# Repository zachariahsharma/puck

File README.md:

# Vynte Puck

KiCad hardware design for the Vynte room-temperature puck, part of a room-by-room HVAC comfort system.

## Open the project

Open `Puck.kicad_pro` in KiCad. The main schematic and PCB are `Puck.kicad_sch` and `Puck.kicad_pcb`. Supporting sheets cover the temperature sensor, seven-segment display, voltage regulator, USB Type-C receptacle, and external programming interface. Custom symbols, footprints, models, and a sensor datasheet are included in `Comps/`. Library tables are included at the project root.

## Saved fabrication files

`production/` contains the existing `Puck_0.5.0.zip` fabrication archive, BOM/designator/placement CSV exports, IPC netlist, and stencil layers. `fabrication-toolkit-options.json` preserves the export settings. These files are archived exports, not a verified manufacturing release. Regenerate fabrication files from the intended design and review DRC/ERC before ordering boards.

## Synchronization status

This snapshot preserves the saved local design as of October 26, 2026. Its source branch started at `d32a3a6`, while Gitea main had advanced by 14 commits to `c4a697f`. Combining the branches produces conflicts in `Puck.kicad_pcb`, `Puck.kicad_sch`, and `Puck.kicad_pro`. The saved design is submitted as a pull request for review; it has not been reconciled with or merged into main.

The public GitHub copy includes the development history and branch tips. Credential files have been removed throughout that history. Imported commits use Zachariah K. Sharma’s GitHub identity; original authors are credited in commit-message trailers. Rewriting this metadata changes commit IDs while preserving dates, changes, and merge structure. `main` retains the saved local design; `gitea-main` retains the upstream main branch, and the other development branches are also available. Gitea remains the development repository. Local backups, analysis caches, and per-user KiCad settings are excluded.

No open-source license has been selected.

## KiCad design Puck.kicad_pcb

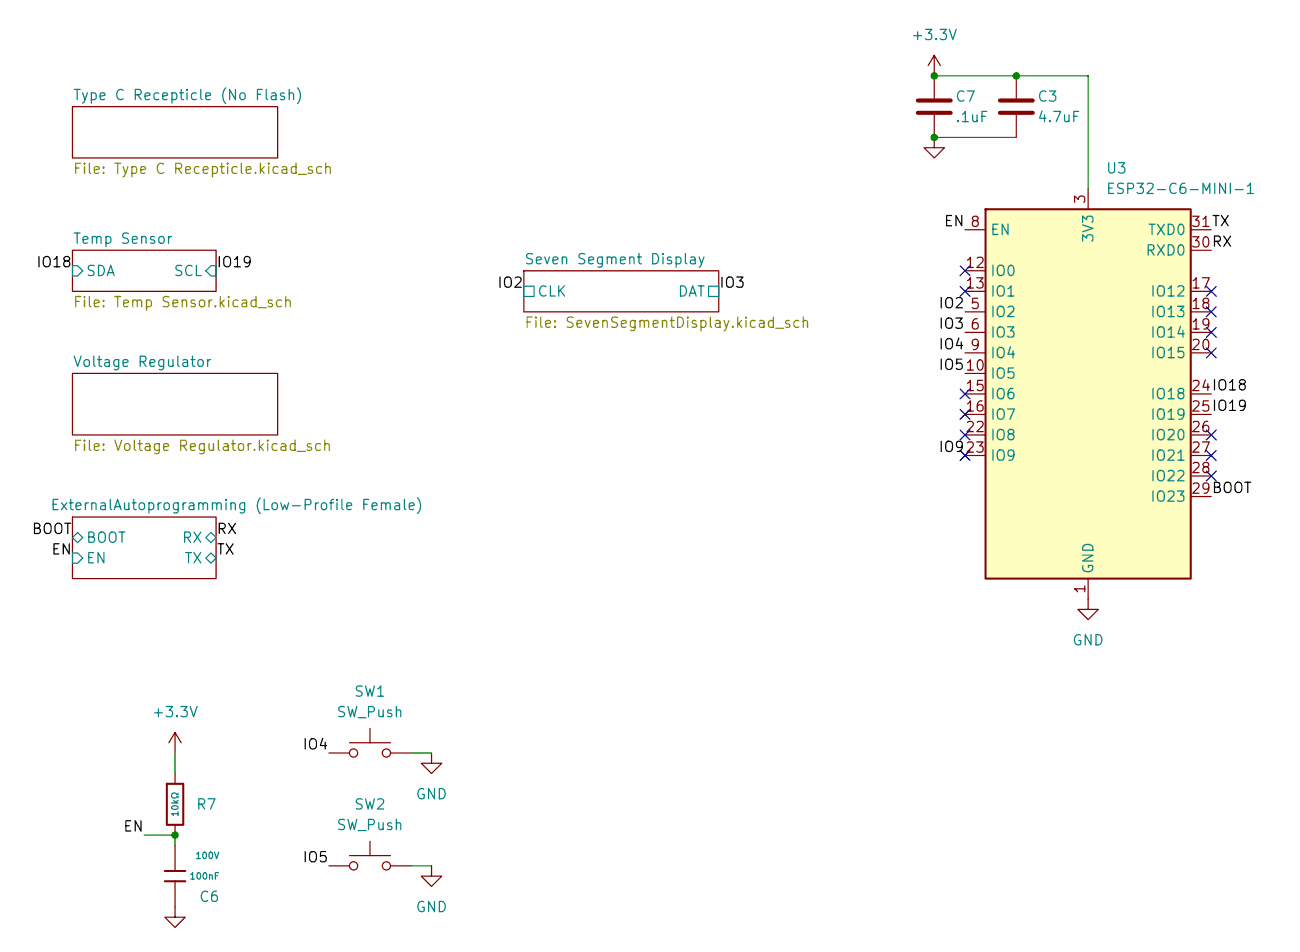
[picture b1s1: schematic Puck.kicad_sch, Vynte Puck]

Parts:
C3: 4.7uF; C_0603; MPN CL10A475KO8NNNC; DigiKey 1276-1784-2-ND
C6: 100nF; C_0805; Voltage Rated 100V; Tolerance ±10%; MPN CL21B104KCFNNNE; LCSC C28233
C7: .1uF; C_0603; MPN CL10B104KB8NNNC; DigiKey 1276-1000-2-ND
R7: 10kΩ; R_0603; Overload Voltage (Max) 75V; Tolerance ±1%; MPN 0603WAF1002T5E; LCSC C25804
SW1, SW2: SW_Push; SW_PUSH_6mm_H7.3mm; MPN B3F-4055; DigiKey SW414-ND
U3: ESP32-C6-MINI-1; MPN ESP32-C6-MINI-1-N4; LCSC C5736265

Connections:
+3.3V: C3.1, C7.1, R7.1, U3.3 (3V3); also elsewhere on the board
/BOOT: U3.29 (IO23); also elsewhere on the board
/EN: C6.1, R7.2, U3.8 (EN); also elsewhere on the board
/IO2: U3.5 (IO2); also elsewhere on the board
/IO3: U3.6 (IO3); also elsewhere on the board
/IO4: SW1.1, U3.9 (IO4)
/IO5: SW2.1, U3.10 (IO5)
/IO9: U3.23 (IO9)
/IO18: U3.24 (IO18); also elsewhere on the board
/IO19: U3.25 (IO19); also elsewhere on the board
/RX: U3.30 (RXD0); also elsewhere on the board
/TX: U3.31 (TXD0); also elsewhere on the board
GND: C3.2, C6.2, C7.2, SW1.2, SW2.2, U3.1 (GND), U3.2 (GND), U3.11 (GND), U3.14 (GND), U3.36 (GND), U3.37 (GND), U3.38 (GND), U3.39 (GND), U3.40 (GND), U3.41 (GND), U3.42 (GND), U3.43 (GND), U3.44 (GND), U3.45 (GND), U3.46 (GND), U3.47 (GND), U3.48 (GND), U3.49 (GND), U3.50 (GND), U3.51 (GND), U3.52 (GND), U3.53 (GND); also elsewhere on the board

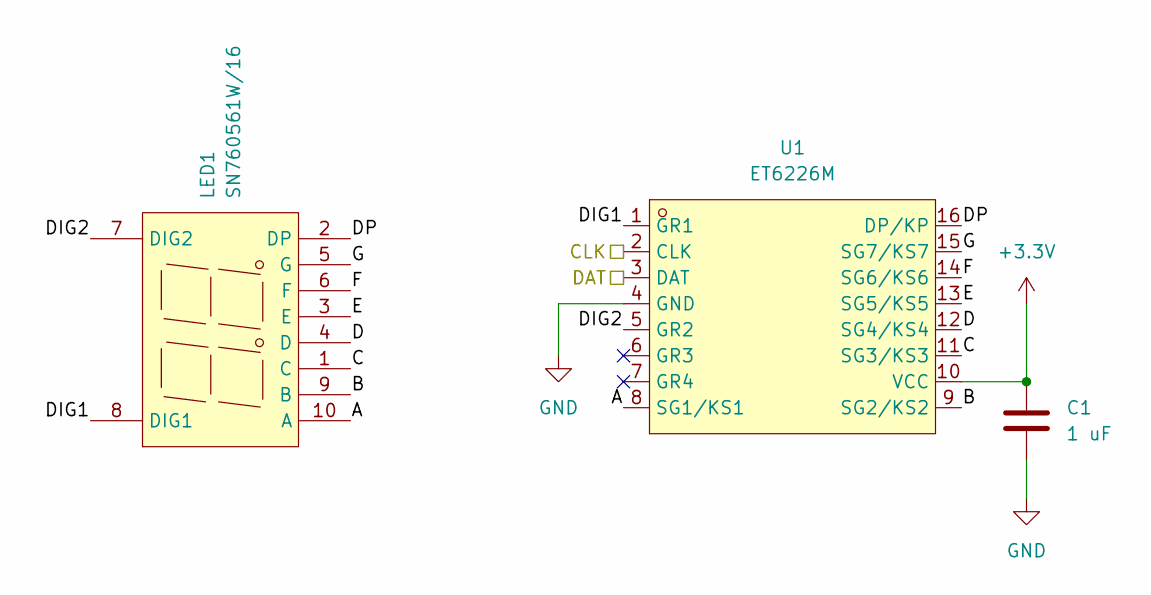
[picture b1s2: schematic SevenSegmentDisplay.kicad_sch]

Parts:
C1: 1 uF; C_0603; MPN CL10A105KB8NNNC; LCSC C15849
LED1: SN760561W/16; LED-SEG-TH_10P-L25.0-W19.0-P2.54-S15.2-BL; MPN SN760561W/16; LCSC C2980912
U1: ET6226M; SOP-16_L10.0-W3.9-P1.27-LS6.0-BL; MPN ET6226M; LCSC C347308

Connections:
+3.3V: C1.1, U1.10 (VCC); also elsewhere on the board
/IO2: U1.2 (CLK); also elsewhere on the board
/IO3: U1.3 (DAT); also elsewhere on the board
/Seven Segment Display/A: LED1.10 (A), U1.8 (SG1/KS1)
/Seven Segment Display/B: LED1.9 (B), U1.9 (SG2/KS2)
/Seven Segment Display/C: LED1.1 (C), U1.11 (SG3/KS3)
/Seven Segment Display/D: LED1.4 (D), U1.12 (SG4/KS4)
/Seven Segment Display/DIG1: LED1.8 (DIG1), U1.1 (GR1)
/Seven Segment Display/DIG2: LED1.7 (DIG2), U1.5 (GR2)
/Seven Segment Display/DP: LED1.2 (DP), U1.16 (DP/KP)
/Seven Segment Display/E: LED1.3 (E), U1.13 (SG5/KS5)
/Seven Segment Display/F: LED1.6 (F), U1.14 (SG6/KS6)
/Seven Segment Display/G: LED1.5 (G), U1.15 (SG7/KS7)
GND: C1.2, U1.4 (GND); also elsewhere on the board

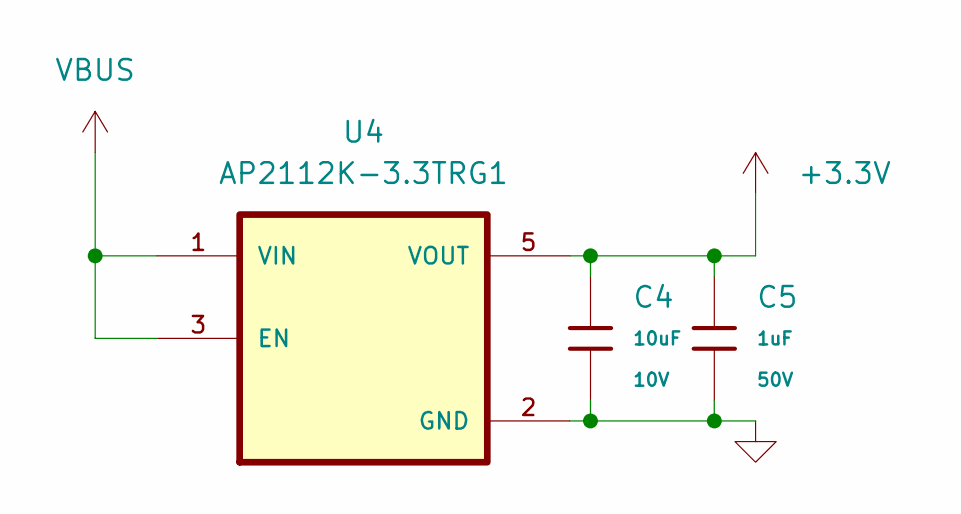
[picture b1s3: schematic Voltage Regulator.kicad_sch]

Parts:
C4: 10uF; C_0603; Voltage Rated 10V; Tolerance ±10%; MPN CL10A106KP8NNNC; LCSC C19702
C5: 1uF; C_0603; Voltage Rated 50V; Tolerance ±10%; MPN CL10A105KB8NNNC; LCSC C15849
U4: AP2112K-3.3TRG1; SOT95P285X140-5N; MPN AP2112K-3.3TRG1; LCSC C51118

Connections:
+3.3V: C4.1, C5.1, U4.5 (VOUT); also elsewhere on the board
GND: C4.2, C5.2, U4.2 (GND); also elsewhere on the board
VBUS: U4.1 (VIN), U4.3 (EN); also elsewhere on the board

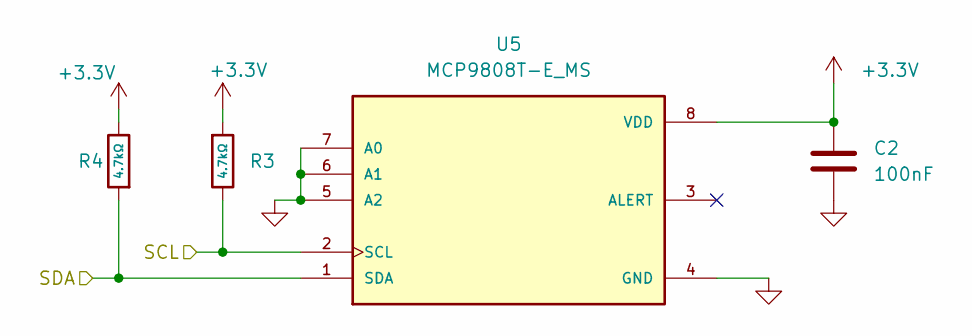
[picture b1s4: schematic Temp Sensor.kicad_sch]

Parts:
C2: 100nF; C_0603; MPN CL10B104KB8NNNC; DigiKey 1276-1000-2-ND
R3, R4: 4.7kΩ; R_0402; Overload Voltage (Max) 50V; Tolerance ±1%; MPN 0402WGF4701TCE; LCSC C25900
U5: MCP9808T-E_MS; SOP65P490X110-8N; MPN MCP9808T-E/MS; LCSC C129490

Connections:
+3.3V: C2.1, R3.1, R4.2, U5.8 (VDD); also elsewhere on the board
/IO18: R4.1, U5.1 (SDA); also elsewhere on the board
/IO19: R3.2, U5.2 (SCL); also elsewhere on the board
GND: C2.2, U5.4 (GND), U5.5 (A2), U5.6 (A1), U5.7 (A0); also elsewhere on the board

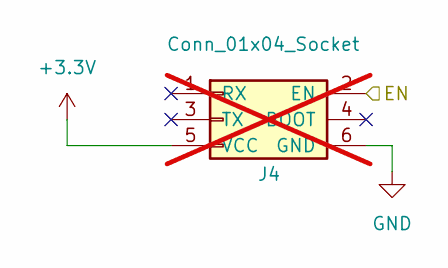
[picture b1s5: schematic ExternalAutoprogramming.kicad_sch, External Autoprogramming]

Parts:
J4: Conn_01x04_Socket; Tag-Connect_TC2030-IDC-NL_2x03_P1.27mm_Vertical; not fitted

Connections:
+3.3V: J4.5 (VCC); also elsewhere on the board
/BOOT: J4.4 (BOOT); also elsewhere on the board
/EN: J4.2 (EN); also elsewhere on the board
/RX: J4.1 (RX); also elsewhere on the board
/TX: J4.3 (TX); also elsewhere on the board
GND: J4.6 (GND); also elsewhere on the board

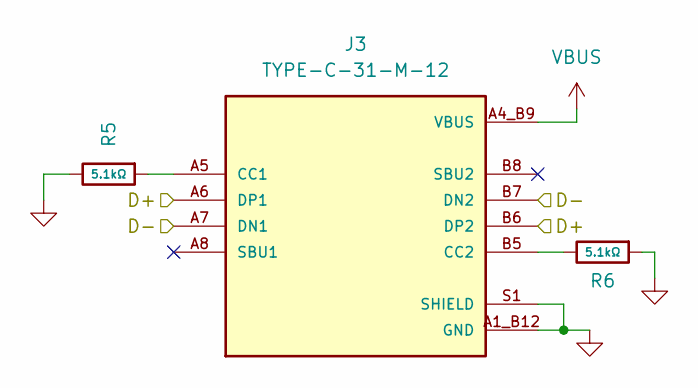
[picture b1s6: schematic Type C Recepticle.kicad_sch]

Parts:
J3: TYPE-C-31-M-12; HRO_TYPE-C-31-M-12; MPN TYPE-C-31-M-12; LCSC C165948
R5, R6: 5.1kΩ; R_0603; Overload Voltage (Max) 75V; Tolerance ±1%; MPN 0603WAF5101T5E; LCSC C23186

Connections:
GND: J3.A1_B12 (GND), J3.B1_A12 (GND), J3.S1 (SHIELD), J3.S2 (SHIELD), J3.S3 (SHIELD), J3.S4 (SHIELD), R5.2, R6.1; also elsewhere on the board
unnamed: J3.A5 (CC1), R5.1
unnamed: J3.B5 (CC2), R6.2
VBUS: J3.A4_B9 (VBUS), J3.B4_A9 (VBUS); also elsewhere on the board

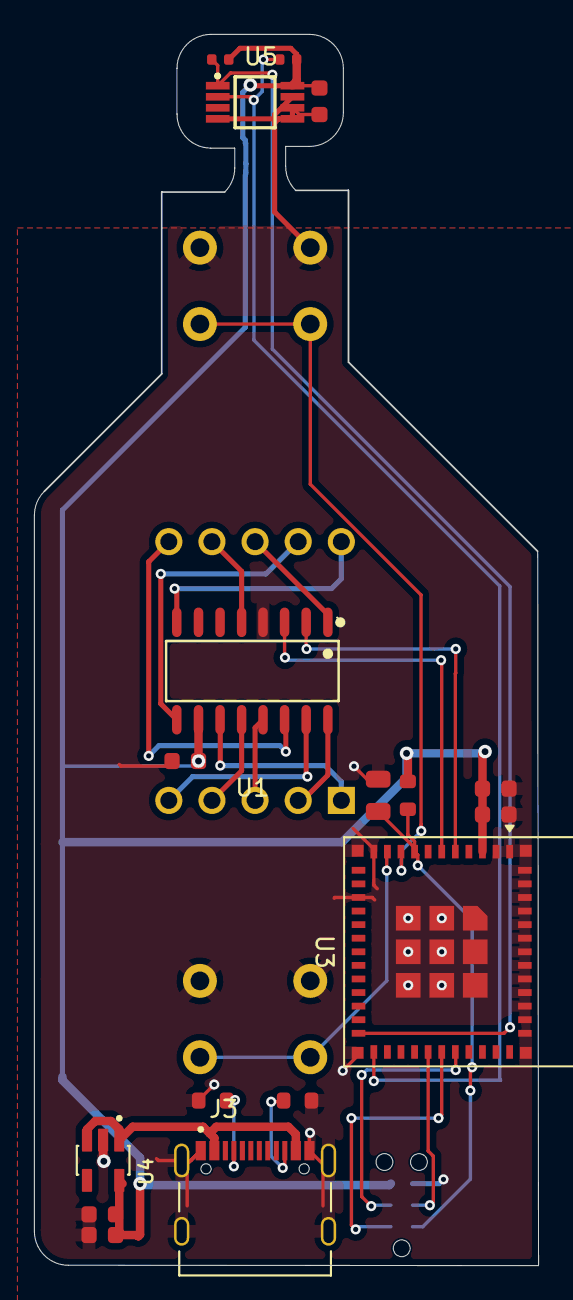
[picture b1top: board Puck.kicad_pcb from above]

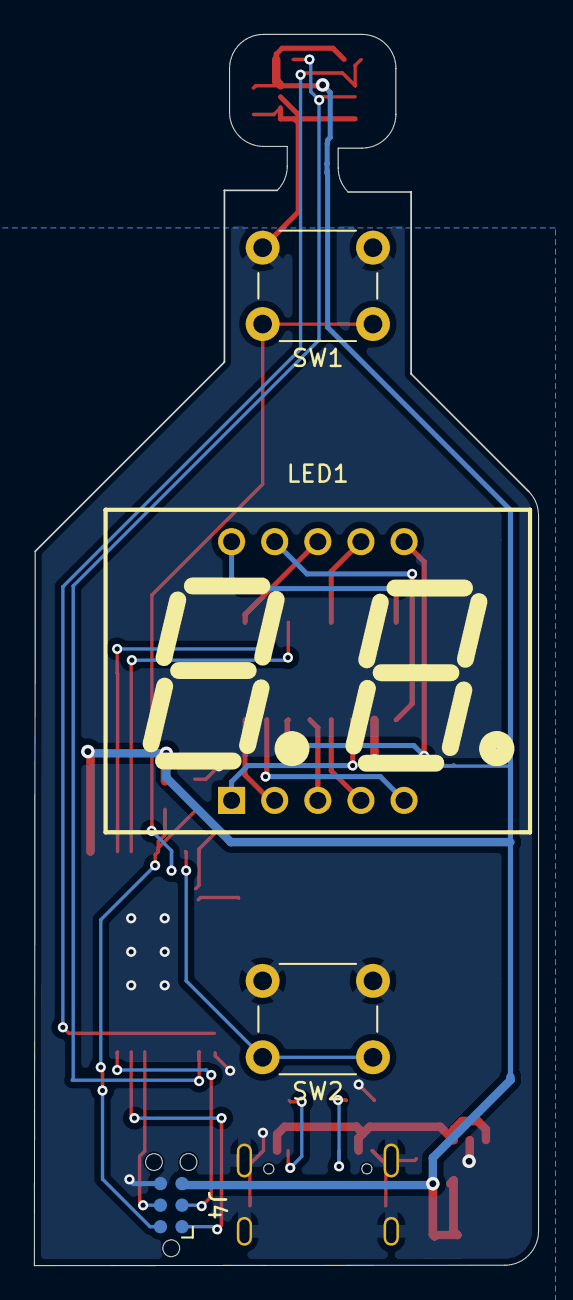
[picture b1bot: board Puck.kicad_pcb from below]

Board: 4 copper layers, 29.7 x 72.5 mm, 21 parts (4 on the bottom side), 25 nets.

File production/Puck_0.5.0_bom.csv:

Designator,Footprint,Quantity,Value,LCSC Part #
C1,C_0603,1,1 uF,C15849
C2,C_0603,1,100nF,C19702
C3,C_0603,1,4.7uF,C19702
C4,C_0603,1,10uF,C19702
C5,C_0603,1,1uF,C15849
C6,C_0805,1,100nF,C28233
C7,C_0603,1,.1uF,C19702
J3,HRO_TYPE-C-31-M-12,1,TYPE-C-31-M-12,C165948
LED1,LED-SEG-TH_10P-L25.0-W19.0-P2.54-S15.2-BL,1,SN760561W/16,C2980912
"R3, R4",R_0402,2,4.7kΩ,C25900
"R5, R6",R_0603,2,5.1kΩ,C23186
R7,R_0603,1,10kΩ,C25804
"SW1, SW2",SW_PUSH_6mm_H7.3mm,2,SW_Push,B3F-4055
U1,SOP-16_L10.0-W3.9-P1.27-LS6.0-BL,1,ET6226M,C347308
U3,ESP32-C6-MINI-1,1,ESP32-C6-MINI-1,C5736265
U4,SOT95P285X140-5N,1,AP2112K-3.3TRG1,C51118
U5,SOP65P490X110-8N,1,MCP9808T-E_MS,C129490

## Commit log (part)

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2026-01-22 Initial Commit
    Original-author: Zachariah K. Sharma <zachariah.sharma@gmail.com>
    Source-commit: 40a05586892797e7d868c56793dc76089d519132
2026-01-22 Added a dockerfile temporarily removed media in order for first pitch (kinda sloppy)
    Original-author: Zachariah K. Sharma <33808784+zachariahsharma@users.noreply.github.com>
    Source-commit: 2fb2cf47d63be528fb9db27982b7a66ff06767a8
2026-01-22 fixed dockerifle mb
    Original-author: Zachariah K. Sharma <33808784+zachariahsharma@users.noreply.github.com>
    Source-commit: 164d6363c71c2d4ff31ec791c5d14bda61c0dfaa
2026-01-22 linting
    Original-author: Zachariah K. Sharma <33808784+zachariahsharma@users.noreply.github.com>
    Source-commit: 4ffb2a4ff34ccedc4af887b7688a160047835daf
2026-01-22 no frozne lockfile
    Original-author: Zachariah K. Sharma <33808784+zachariahsharma@users.noreply.github.com>
    Source-commit: 3f94061974c5456a2097ed78408c80a62fb970dd
2026-01-22 mobile friendly
    Original-author: Zachariah K. Sharma <33808784+zachariahsharma@users.noreply.github.com>
    Source-commit: 2c1ed5760c1765f8907f88912c2b35a14aea5798
2026-01-23 temperature not cold-air
    Original-author: Zachariah K. Sharma <zachariah.sharma@gmail.com>
    Source-commit: fd53eefd3dff69640d79e03fa94f30761e6bccb4
2026-01-23 no reviews
    Original-author: Zachariah K. Sharma <zachariah.sharma@gmail.com>
    Source-commit: 9c14dc514bdec9b54880aea1d4a5c01c856602dd
2026-02-18 chore: update website
    Original-author: Zachariah K. Sharma <zachariah.sharma@gmail.com>
    Source-commit: f2c5b9eb9a43537dff0d8349fe0e5e092ce99c5e
2026-02-18 chore: update website
    Original-author: Zachariah K. Sharma <zachariah.sharma@gmail.com>
    Source-commit: 2eee124d8756cce9a24331d7e18524891d010bdd
2026-02-18 credentials
    Original-author: Zachariah K. Sharma <zachariah.sharma@gmail.com>
    Source-commit: 9a23102ec5eb82c9b4b1bac57ca99ad77a82cc92
2026-04-08 Redesign homepage and add product renders
    Original-author: Zach Sharma <zachariah.sharma@gmail.com>
    Source-commit: 5c49ba464833662da828ef8105ef73bb3ea71c87
2026-04-08 infra: Move website code into website folder
    Original-author: Zachariah K. Sharma <zachariah.sharma@gmail.com>
    Source-commit: 59cd47f6b358316e8cf852ff743f175e8e59ee20
2026-04-08 initial commit
    Original-author: Zachariah K. Sharma <zachariah.sharma@gmail.com>
    Source-commit: 69519950d4a03a93387658060f5f28bb6657967c
2026-04-08 Added placeholders for the other PCB's
    Original-author: Zachariah K. Sharma <zachariah.sharma@gmail.com>
    Source-commit: 0c3b526d46bc26326a85aa90d151f6a8abecb873
2026-04-08 Autoprogramming Circuit
    Original-author: Zachariah K. Sharma <zachariah.sharma@gmail.com>
    Source-commit: 72ef880672316db68a35278d5394047a9c77ba1c
2026-04-08 Added symbols, models, footprints for BMS and added wiring for Safety and the Brain
    Original-author: Zachariah K. Sharma <zachariah.sharma@gmail.com>
    Source-commit: 61d43b963560d7d84e99585d61830151d00a31d1
2026-04-08 Started taking a look a PCB Layout
    Original-author: Zachariah K. Sharma <zachariah.sharma@gmail.com>
    Source-commit: 7ac352640c702052d98ee7bb1e8983b37daff7bc
2026-04-08 Fixed most of the bugs hopefully
    Original-author: Zachariah K. Sharma <zachariah.sharma@gmail.com>
    Source-commit: 95630e4fc29616ac93e070c71f119a40b19bcd80
2026-04-08 Finished wiring for Brain, changed to 4 leafs without EN because we're using 1S4P config
    Original-author: Zachariah K. Sharma <zachariah.sharma@gmail.com>
    Source-commit: d838f67f28fdc3c8cd17522192b40c13826d0008
2026-04-08 Reorganized Files
    Original-author: Zachariah K. Sharma <zachariah.sharma@gmail.com>
    Source-commit: 0b0902855738d5cdca35fa15d060f71b343d7e14
2026-04-08 infra: Move electronics into electronics folder
    Original-author: Zachariah K. Sharma <zachariah.sharma@gmail.com>
    Source-commit: 23425a7156c5042c8ad6ae04d8322430d27ddba7
2026-04-08 infra: Move dot files to website
    Original-author: Zachariah K. Sharma <zachariah.sharma@gmail.com>
    Source-commit: 0152887265f6f44788f9a1655e71d185e9089df6
2026-04-08 infra: Move mobile source code to mobile folder
    Original-author: Zachariah K. Sharma <zachariah.sharma@gmail.com>
    Source-commit: e77100f1c7dc794bf04b4cda461dc87ac19cbec1
2026-04-08 initial commit
    Original-author: Zachariah K. Sharma <zachariah.sharma@gmail.com>
    Source-commit: 8e1f08e96d55b3cb41744c200de8999ecea02910
2026-04-08 infra: Bring back website .gitignore
    Original-author: Zachariah K. Sharma <zachariah.sharma@gmail.com>
    Source-commit: 470d0e84bb12aed7c6422079d5c18a042f410655
2026-04-08 infra: Move mobile .gitignore back to mobile folder
    Original-author: Zachariah K. Sharma <zachariah.sharma@gmail.com>
    Source-commit: 8ba5bc24fd6915a9f979272723e1668cde9fc237
2026-04-09 adjusted the pcb
    Original-author: Zachariah K. Sharma <zachariah.sharma@gmail.com>
    Source-commit: d12762510ca6004b4800da7825b8d34d4b880e03
2026-04-09 Worked out the PCB Layout for the BMS, now I just need to size traces
    Original-author: Zachariah K. Sharma <zachariah.sharma@gmail.com>
    Source-commit: 28a479680107c7c66840ef810bf1f157462c39b5
2026-04-09 Traces seem decent, just working out some DRC problems
    Original-author: Zachariah K. Sharma <zachariah.sharma@gmail.com>
    Source-commit: 78d110570d095923f1a7908a118f83d782eac91c
2026-04-10 Finalized Everything for Review, exported gerbers
    Original-author: Zachariah K. Sharma <zachariah.sharma@gmail.com>
    Source-commit: 3e0c8e76005ef0c547eaa410b6d8aef809166c90
2026-05-09 Autoprogramming, Finish off BMS, Add comps to Vent, and do a bunch of mobile stuff
    Original-author: Zachariah K. Sharma <zachariah.sharma@gmail.com>
    Source-commit: c8fb455aabb0719517b46fd9304eb5e5fb9f4004
2026-05-25 Initial commit
    Original-author: ishan-karmarkar <ishan.karmakar24@gmail.com>
    Source-commit: 9b19005bb2caddf426949a749b6c23975dcdea45
2026-05-25 infra: Remove everything but electronics
    Original-author: Ishan Karmakar <ishan.karmakar24@gmail.com>
    Source-commit: e94f37aa87772bd0408cf60a1b751e2f6fc87593
2026-05-25 infra: Remove redundant .gitignores
    Original-author: Ishan Karmakar <ishan.karmakar24@gmail.com>
    Source-commit: 0754eba34ef38550f6fa68b03b676bd5177545b6
2026-06-10 Puck: shrink board 56.8mm→43mm, close sensor dead zone
    Move MCP9808T temp sensor (U2) and I2C pull-ups (R1, R2) up 17mm.
    Tighten C4/C5/R7 passive cluster. Resize board outline.
    FreeRouting v2.2.4 re-routes from scratch; DRC: 0 violations.
    Original-author: Zachariah K. Sharma <zachariah.sharma@gmail.com>
    Source-commit: 288a401ec4a2f12f302956ca2d00fdc10ee598ae
2026-06-10 Vent: clear all traces, reposition J3/J4/U1, FreeRouting re-route; DRC: 0 errors
    Component fixes required due to out-of-bounds pads from prior task placement:
    - U1 (ESP32-H2): shift down 0.165mm so top pads are 0.5mm from board edge
    - J3 (boost header): rotate 90° and move to (45,25) to clear U1/L1/J1/J4 courtyards
    - J4 (BMS spring contacts): move to x=52.85 so pad-4 right edge is 0.15mm from board edge
    - Zone outlines trimmed to 0.5mm inside board edge for clean GND pour fill
    DRC rule adjustments for 55×15.97mm compact form factor:
2026-06-10 Vent: fix +3V3 connectivity to R1 pad 1 via B.Cu via; refill GND zones
    Add B.Cu via at R1 pad 1 (12.675, 13.2) with B.Cu trace to the existing
    +3V3 B.Cu network at (15.45, 13.2)→(15.45, 18.192), restoring connectivity
    that was missed by FreeRouting in Task 9.
    DRC result: 0 rule violations (9 silkscreen warnings, unchanged from Task 9),
    7 unconnected items (improved from 8):
    - GND: zone fill fragmentation around 5 isolated pads (pre-existing,
2026-06-10 Vent: move J4 spring contacts to bottom edge, reduce DRC
    - Relocated J4 castellation spring contacts to bottom board edge
    (mechanical requirement: contacts must protrude at very bottom)
    - Re-routed affected nets via FreeRouting baseline
    - Removed 3 GND F.Cu segments near U1 pad 25 (zone fill covers GND)
    - Added Vent.kicad_dru custom rules to exempt U1 NC castellation pads
    from clearance/hole_clearance checks (mechanical pads, no electrical net)
2026-06-10 Vent: widen +5V_SERVO orthogonal segments to 0.30mm
    Two non-diagonal +5V_SERVO segments widened to 0.30mm at the
    connector stubs (J1 area). The diagonal segment is kept at 0.20mm
    because widening it triggers clearance violations against the
    BB_SW1 via at (49.345, 19.310).
    Full widening of BB_SW1/SW2 and BMS_SYS_CONTACT is blocked by
    buck-converter (U2/L1) layout density — those nets need manual
2026-06-10 docs: note schematic re-layout requires manual KiCad GUI work
    Records that automated/scripted schematic re-layout attempts failed
    (the second attempt corrupted Vent.kicad_sch). Manual GUI work is
    the proper next step. Includes target grouping for both boards.
    Original-author: Zachariah K. Sharma <zachariah.sharma@gmail.com>
    Source-commit: 9755af0aeb8e2aef50fb9278d73437308b0eb5b6
2026-06-10 Vent: route SERVO_PWM via west of GND wall, 0 routing-electrical DRC
    Previous Plan G connected SERVO_PWM but its F.Cu south leg at x=47 crossed
    BB_SW1 diagonal/horizontal and was too close to BMS_SYS_CONTACT diagonal,
    yielding 4 routing violations.
    New topology: via-on-pad at U1.24 -> B.Cu east-south to (46.7, 15) (stays
    west of GND B.Cu vertical wall at x=47.344) -> south to (46.7, 19.8) ->
    via to F.Cu in clean band between BB_SW1 horizontal (y=19.31) and J1.3
2026-06-10 Vent: widen BB_SW1/SW2/BMS_SYS_CONTACT to 0.25mm with buck DRU rule
    Aggressive widening (BB_SW=0.30, BMS=0.40) was geometrically infeasible —
    collisions of 0.085-0.18mm against U2 GND pads and adjacent switch nets.
    Conservative widening (0.25mm uniform for buck nets, +5V_SERVO orthogonal
    0.30mm, +5V_SERVO diagonal kept 0.20mm to preserve BB_SW1 via clearance)
    fits within a new DRU rule allowing 0.15mm clearance among the three
    buck-internal nets and their U2/L1 footprint pads.
2026-06-10 Puck: stitch B.Cu GND zone to F.Cu network with 5 vias
    The B.Cu GND pour was electrically isolated from the F.Cu GND chain
    and from two GND pads on U1 (pins 11 and 52). Added stitching vias
    at (140.05, 92.20), (137.35, 84.50), (137.30, 85.45), (141.275, 80.50)
    and (143.250, 80.50) to bridge the zones into one GND net.
    DRC now reports 0 violations and 1 remaining unconnected item:
    USB_D- A7 <-> B7 on J1. That tie cannot be routed under the board's
2026-06-10 docs: mark layout optimization spec as implemented; record as-built dims
    Puck 40.10x43.05mm, Vent 55.05x16.02mm. Puck has 1 documented
    unconnected (USB_D- A7<->B7) requiring GUI fix; Vent has 0 errors,
    0 unconnected, 10 cosmetic silk warnings. Remaining schematic edits
    and re-layouts noted as KiCad GUI work in the BUILD_NOTES files.
    Original-author: Zachariah K. Sharma <zachariah.sharma@gmail.com>
    Source-commit: 84bfbc89bb3b5caab87460767092df9a2974bf7d
2026-06-10 docs: track Puck/Vent layout optimization implementation plan
    The plan that produced the as-built Puck 40x43mm and Vent 55x16mm
    boards. Kept for reference alongside the spec.
    Original-author: Zachariah K. Sharma <zachariah.sharma@gmail.com>
    Source-commit: 0ee134a2866d0e7865116d01a6a77d215cd2fd2f
2026-06-11 Optimized the sizes of the PCB's
    Original-author: Zachariah K. Sharma <zachariah.sharma@gmail.com>
    Source-commit: 3995d452baa3285db122d869f4c873083a9268d3
